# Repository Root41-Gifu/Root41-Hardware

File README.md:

# Root41-Hardware
Root41のハードウェア開発リポジトリです。

3D設計のリンクはこちら↓

[Root41 2021-2022](https://a360.co/2STp2Ga)

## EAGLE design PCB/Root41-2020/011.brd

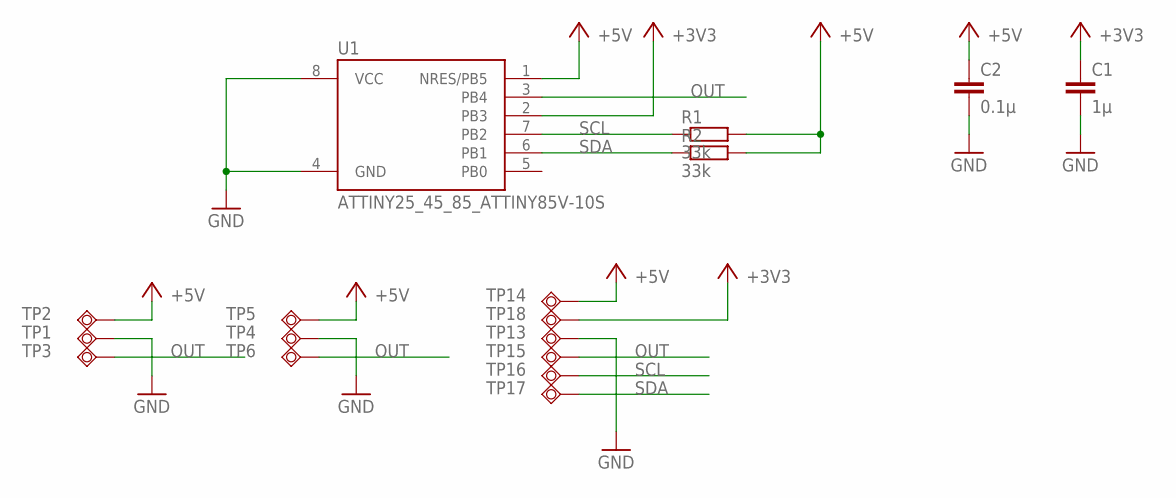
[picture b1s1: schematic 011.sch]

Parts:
C1: 1μ; C0603
C2: 0.1μ; C0603
R1, R2: 33k; R0603
TP1, TP3, TP4, TP6, TP13, TP15, TP16, TP17, TP18: TPSQTP11R; TP11R
TP2, TP5, TP14: TPSQTP11SQ; TP11SQ
U1: ATTINY25_45_85_ATTINY85V-10S; ATTINY25_45_85_SOIC8_EIAJ_208MIL

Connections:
+3V3: C1.1, TP18.TP, U1.2 (PB3)
+5V: C2.1, R1.2, R2.2, TP2.TP, TP5.TP, TP14.TP, U1.1 (NRES/PB5)
GND: C1.2, C2.2, TP1.TP, TP4.TP, TP13.TP, U1.4 (GND), U1.8 (VCC)
OUT: TP3.TP, TP6.TP, TP15.TP, U1.3 (PB4)
SCL: R1.1, TP16.TP, U1.7 (PB2)
SDA: R2.1, TP17.TP, U1.6 (PB1)

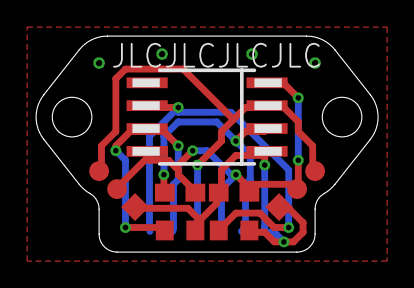
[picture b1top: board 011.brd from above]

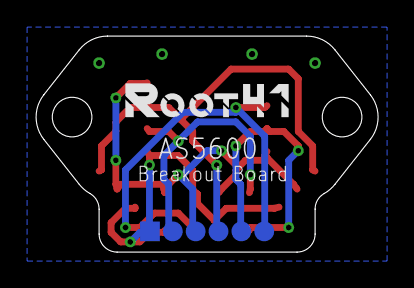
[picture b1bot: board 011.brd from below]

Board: 2 copper layers, 19.0 x 12.0 mm, 17 parts (6 on the bottom side), 6 nets.

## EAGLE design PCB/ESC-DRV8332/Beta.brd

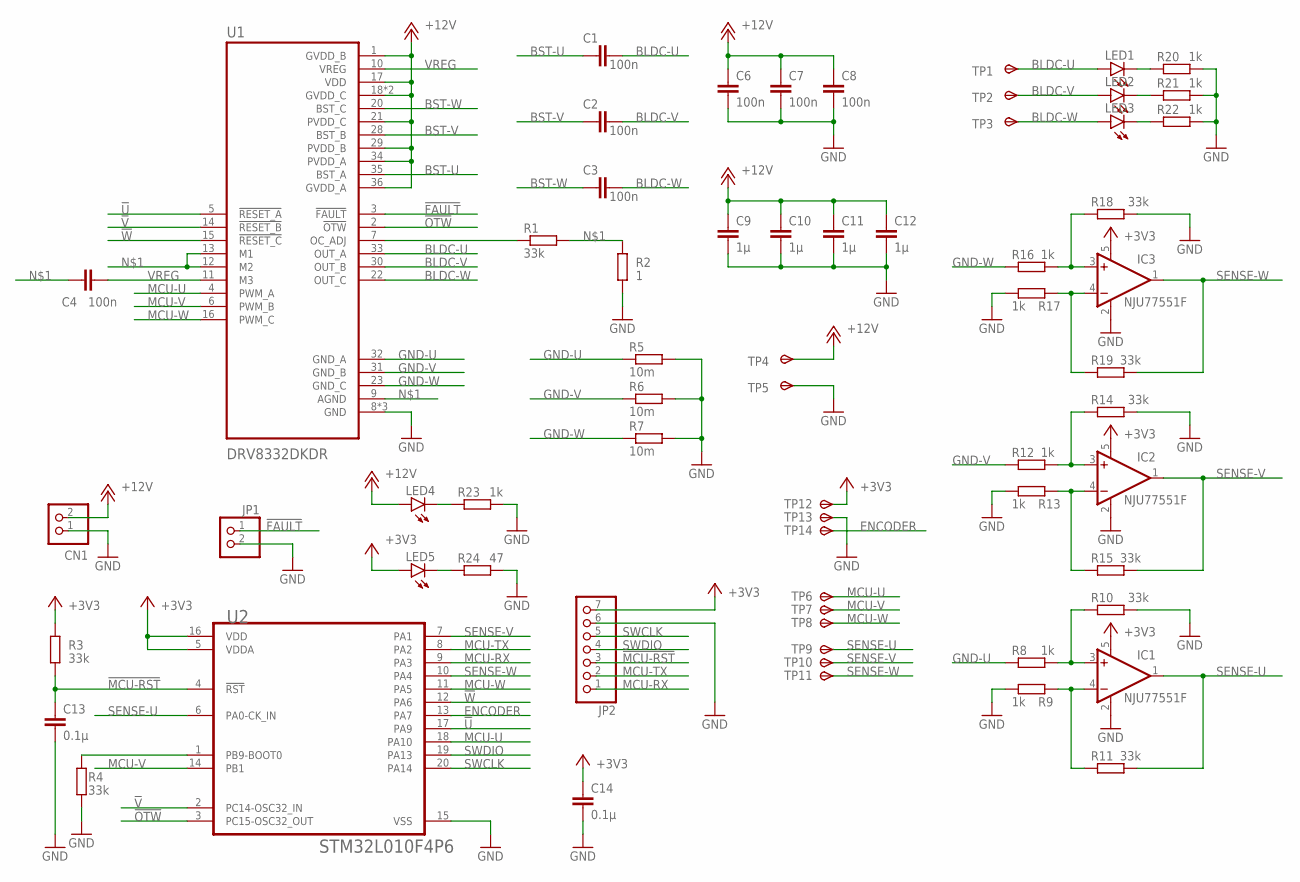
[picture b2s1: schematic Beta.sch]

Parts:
C1, C2, C3, C4, C6, C7, C8: 100n; C0603
C9, C10, C11, C12: 1μ; C0603
C13, C14: 0.1μ; C0603
CN1: B2B-PH-K-S
IC1, IC2, IC3: NJU77551F; SOT23-5
JP1: PINHD-1X2/90; 1X02/90
JP2: PINHD-1X7/90; 1X07/90
LED1, LED2, LED3, LED4, LED5: LEDCHIPLED_0603; CHIPLED_0603
R1, R3, R4, R10, R11, R14, R15, R18, R19: 33k; R0603
R2: 1; R0603
R5, R6, R7: 10m; R3216
R8, R9, R12, R13, R16, R17, R20, R21, R22, R23: 1k; R0603
R24: 47; R0603
TP1, TP2, TP3, TP4, TP5: TPSPAD1-20; P1-20
TP6, TP9, TP12: TPSTP11SQ; TP11SQ
TP7, TP8, TP10, TP11, TP13, TP14: TPSTP11R; TP11R
U1: DRV8332DKDR; SOP65P1420X360-36N
U2: STMICROELECTRONICS_STM32L010F4P6STMICROELECTRONIC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; STMICROELECTRONICS_STM32L010F4P6_2

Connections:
!FAULT: JP1.1, U1.3 (!FAULT)
!MCU-RST: C13.1, JP2.3, R3.1, U2.4 (!RST!)
!OTW: U1.2 (!OTW), U2.3 (PC15-OSC32_OUT)
!U: U1.5 (!RESET_A), U2.17 (PA9)
!V: U1.14 (!RESET_B), U2.2 (PC14-OSC32_IN)
!W: U1.15 (!RESET_C), U2.12 (PA6)
+3V3: C14.1, IC1.5 (V+), IC2.5 (V+), IC3.5 (V+), JP2.7, LED5.A, R3.2, TP12.TP, U2.5 (VDDA), U2.16 (VDD)
+12V: C6.1, C7.1, C8.1, C9.1, C10.1, C11.1, C12.1, CN1.2, LED4.A, TP4.TP, U1.1 (GVDD_B), U1.17 (VDD), U1.18 (GVDD_C), U1.19 (GVDD_C), U1.21 (PVDD_C), U1.29 (PVDD_B), U1.34 (PVDD_A), U1.36 (GVDD_A)
BLDC-U: C1.1, LED1.A, TP1.TP, U1.33 (OUT_A)
BLDC-V: C2.1, LED2.A, TP2.TP, U1.30 (OUT_B)
BLDC-W: C3.1, LED3.A, TP3.TP, U1.22 (OUT_C)
BST-U: C1.2, U1.35 (BST_A)
BST-V: C2.2, U1.28 (BST_B)
BST-W: C3.2, U1.20 (BST_C)
ENCODER: TP14.TP, U2.13 (PA7)
GND: C6.2, C7.2, C8.2, C9.2, C10.2, C11.2, C12.2, C13.2, C14.2, CN1.1, IC1.2 (V-), IC2.2 (V-), IC3.2 (V-), JP1.2, JP2.6, R2.1, R4.1, R5.2, R6.2, R7.2, R9.1, R10.2, R13.1, R14.2, R17.1, R18.2, R20.2, R21.2, R22.2, R23.2, R24.2, TP5.TP, TP13.TP, U1.8 (GND), U1.24 (GND), U1.25 (GND), U2.15 (VSS)
GND-U: R5.1, R8.1, U1.32 (GND_A)
GND-V: R6.1, R12.1, U1.31 (GND_B)
GND-W: R7.1, R16.1, U1.23 (GND_C)
MCU-RX: JP2.1, U2.9 (PA3)
MCU-TX: JP2.2, U2.8 (PA2)
MCU-U: TP6.TP, U1.4 (PWM_A), U2.18 (PA10)
MCU-V: TP7.TP, U1.6 (PWM_B), U2.14 (PB1)
MCU-W: TP8.TP, U1.16 (PWM_C), U2.11 (PA5)
unnamed: C4.1, R1.2, R2.2, U1.9 (AGND), U1.12 (M2), U1.13 (M1)
unnamed: R4.2, U2.1 (PB9-BOOT0)
unnamed: R1.1, U1.7 (OC_ADJ)
unnamed: IC1.3 (+IN), R8.2, R10.1
unnamed: IC2.3 (+IN), R12.2, R14.1
unnamed: IC1.4 (-IN), R9.2, R11.1
unnamed: IC2.4 (-IN), R13.2, R15.1
unnamed: IC3.3 (+IN), R16.2, R18.1
unnamed: IC3.4 (-IN), R17.2, R19.1
unnamed: LED1.C, R20.1
unnamed: LED2.C, R21.1
unnamed: LED3.C, R22.1
unnamed: LED4.C, R23.1
unnamed: LED5.C, R24.1
SENSE-U: IC1.1 (OUT), R11.2, TP9.TP, U2.6 (PA0-CK_IN)
SENSE-V: IC2.1 (OUT), R15.2, TP10.TP, U2.7 (PA1)
SENSE-W: IC3.1 (OUT), R19.2, TP11.TP, U2.10 (PA4)
SWCLK: JP2.5, U2.20 (PA14)
SWDIO: JP2.4, U2.19 (PA13)
VREG: C4.2, U1.10 (VREG), U1.11 (M3)

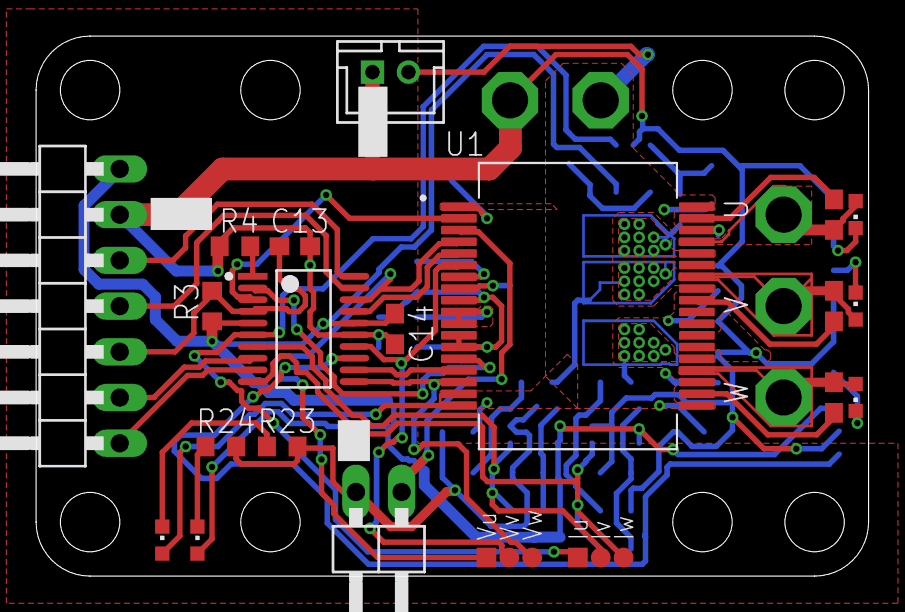
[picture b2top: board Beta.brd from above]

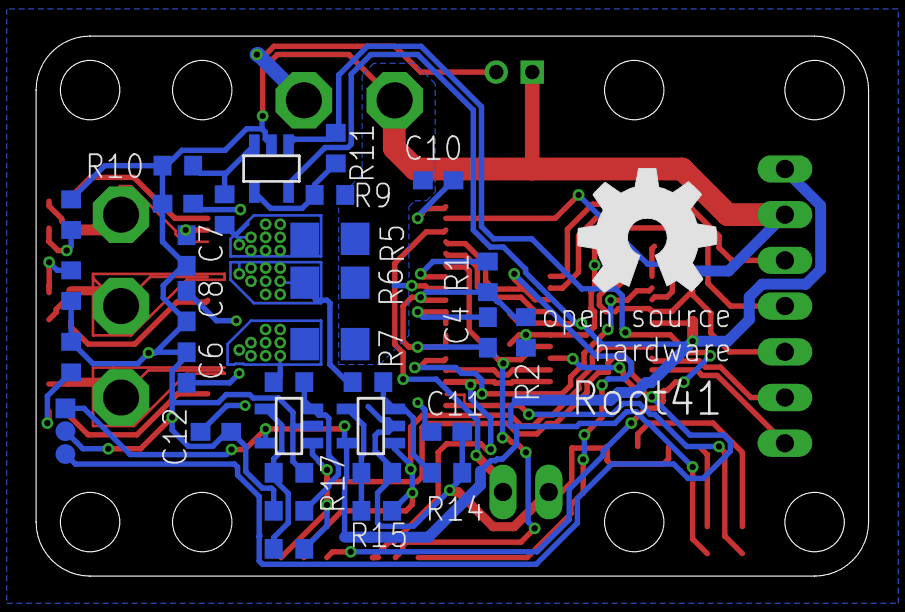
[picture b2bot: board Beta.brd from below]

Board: 2 copper layers, 46.2 x 30.0 mm, 65 parts (35 on the bottom side), 44 nets.

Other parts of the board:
U$1: OSHW_8MM

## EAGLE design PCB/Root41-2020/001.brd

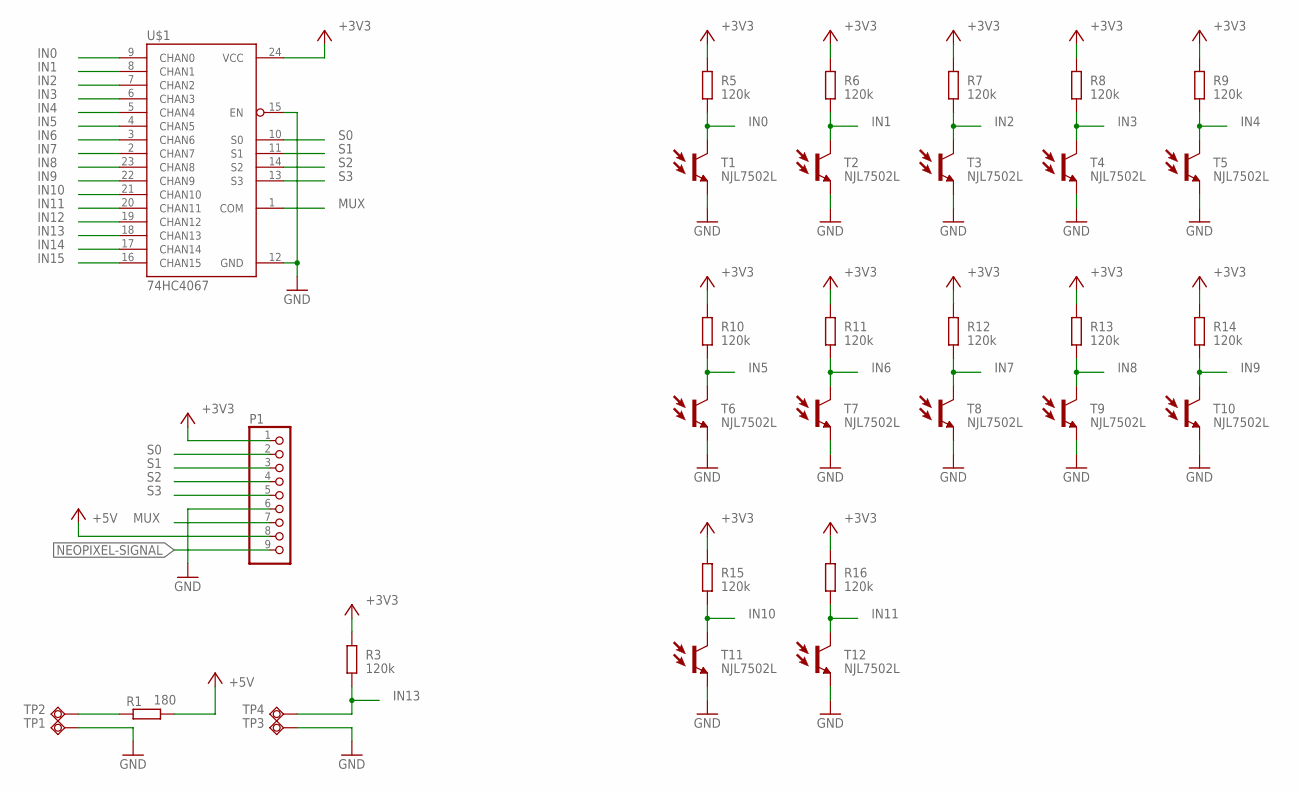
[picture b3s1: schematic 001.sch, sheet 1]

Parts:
P1: S9B-ZR-SM4A-TF; ZH-SM4-SIDE09
R1: 180; R2012
R3, R5, R6, R7, R8, R9, R10, R11, R12, R13, R14, R15, R16: 120k; R0805
T1, T2, T3, T4, T5, T6, T7, T8, T9, T10, T11, T12: NJL7502L; MYPARTS_NJL7502L
TP1, TP3: TPSQTP11R; TP11R
TP2, TP4: TPSQTP11SQ; TP11SQ
U$1: 74HC4067; SPARKFUN_SSOP24

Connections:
+3V3: P1.1, R3.1, R5.1, R6.1, R7.1, R8.1, R9.1, R10.1, R11.1, R12.1, R13.1, R14.1, R15.1, R16.1, U$1.24 (VCC)
+5V: P1.8, R1.2; also elsewhere on the board
GND: P1.6, T1.E, T2.E, T3.E, T4.E, T5.E, T6.E, T7.E, T8.E, T9.E, T10.E, T11.E, T12.E, TP1.TP, TP3.TP, U$1.12 (GND), U$1.15 (EN); also elsewhere on the board
IN0: R5.2, T1.C, U$1.9 (CHAN0)
IN1: R6.2, T2.C, U$1.8 (CHAN1)
IN2: R7.2, T3.C, U$1.7 (CHAN2)
IN3: R8.2, T4.C, U$1.6 (CHAN3)
IN4: R9.2, T5.C, U$1.5 (CHAN4)
IN5: R10.2, T6.C, U$1.4 (CHAN5)
IN6: R11.2, T7.C, U$1.3 (CHAN6)
IN7: R12.2, T8.C, U$1.2 (CHAN7)
IN8: R13.2, T9.C, U$1.23 (CHAN8)
IN9: R14.2, T10.C, U$1.22 (CHAN9)
IN10: R15.2, T11.C, U$1.21 (CHAN10)
IN11: R16.2, T12.C, U$1.20 (CHAN11)
IN12: U$1.19 (CHAN12)
IN13: R3.2, TP4.TP, U$1.18 (CHAN13)
IN14: U$1.17 (CHAN14)
IN15: U$1.16 (CHAN15)
MUX: P1.7, U$1.1 (COM)
unnamed: R1.1, TP2.TP
NEOPIXEL-SIGNAL: P1.9; also elsewhere on the board
S0: P1.2, U$1.10 (S0)
S1: P1.3, U$1.11 (S1)
S2: P1.4, U$1.14 (S2)
S3: P1.5, U$1.13 (S3)

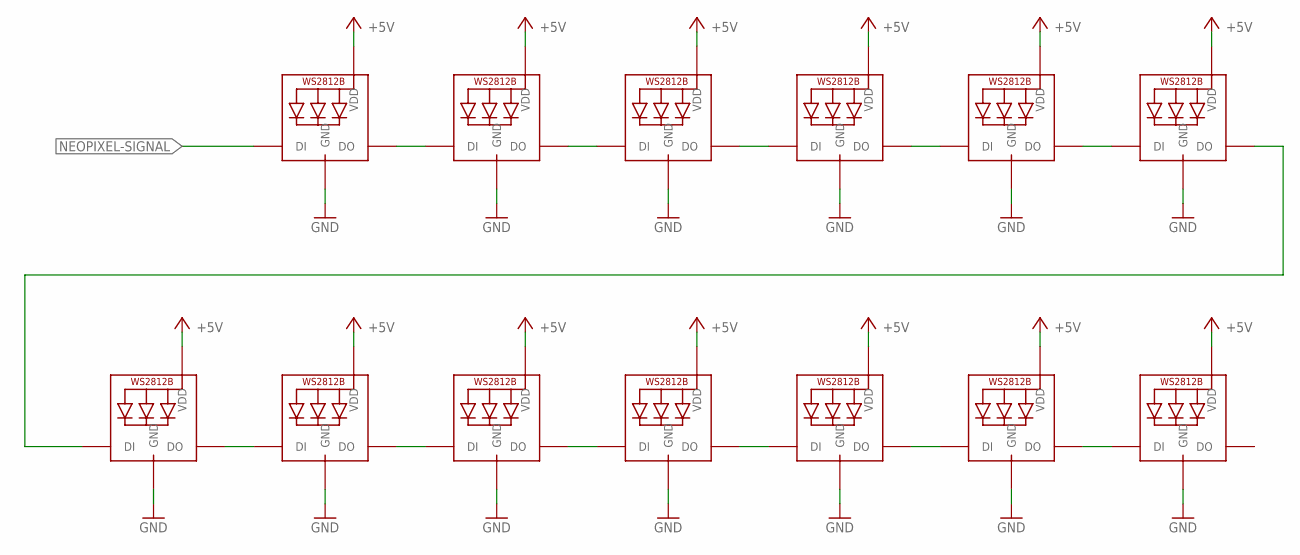
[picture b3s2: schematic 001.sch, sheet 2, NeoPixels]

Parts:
LED1, LED2, LED3, LED4, LED5, LED6, LED7, LED8, LED9, LED10, LED11, LED12, LED13: WS2812B5050; WS2812B

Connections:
+5V: LED1.1-VDD (VDD), LED2.1-VDD (VDD), LED3.1-VDD (VDD), LED4.1-VDD (VDD), LED5.1-VDD (VDD), LED6.1-VDD (VDD), LED7.1-VDD (VDD), LED8.1-VDD (VDD), LED9.1-VDD (VDD), LED10.1-VDD (VDD), LED11.1-VDD (VDD), LED12.1-VDD (VDD), LED13.1-VDD (VDD); also elsewhere on the board
GND: LED1.3-GND (GND), LED2.3-GND (GND), LED3.3-GND (GND), LED4.3-GND (GND), LED5.3-GND (GND), LED6.3-GND (GND), LED7.3-GND (GND), LED8.3-GND (GND), LED9.3-GND (GND), LED10.3-GND (GND), LED11.3-GND (GND), LED12.3-GND (GND), LED13.3-GND (GND); also elsewhere on the board
unnamed: LED2.2-DOUT (DO), LED3.4-DIN (DI)
unnamed: LED1.2-DOUT (DO), LED2.4-DIN (DI)
unnamed: LED3.2-DOUT (DO), LED4.4-DIN (DI)
unnamed: LED4.2-DOUT (DO), LED5.4-DIN (DI)
unnamed: LED5.2-DOUT (DO), LED6.4-DIN (DI)
unnamed: LED6.2-DOUT (DO), LED7.4-DIN (DI)
unnamed: LED7.2-DOUT (DO), LED8.4-DIN (DI)
unnamed: LED8.2-DOUT (DO), LED9.4-DIN (DI)
unnamed: LED9.2-DOUT (DO), LED10.4-DIN (DI)
unnamed: LED10.2-DOUT (DO), LED11.4-DIN (DI)
unnamed: LED11.2-DOUT (DO), LED12.4-DIN (DI)
unnamed: LED12.2-DOUT (DO), LED13.4-DIN (DI)
NEOPIXEL-SIGNAL: LED1.4-DIN (DI); also elsewhere on the board

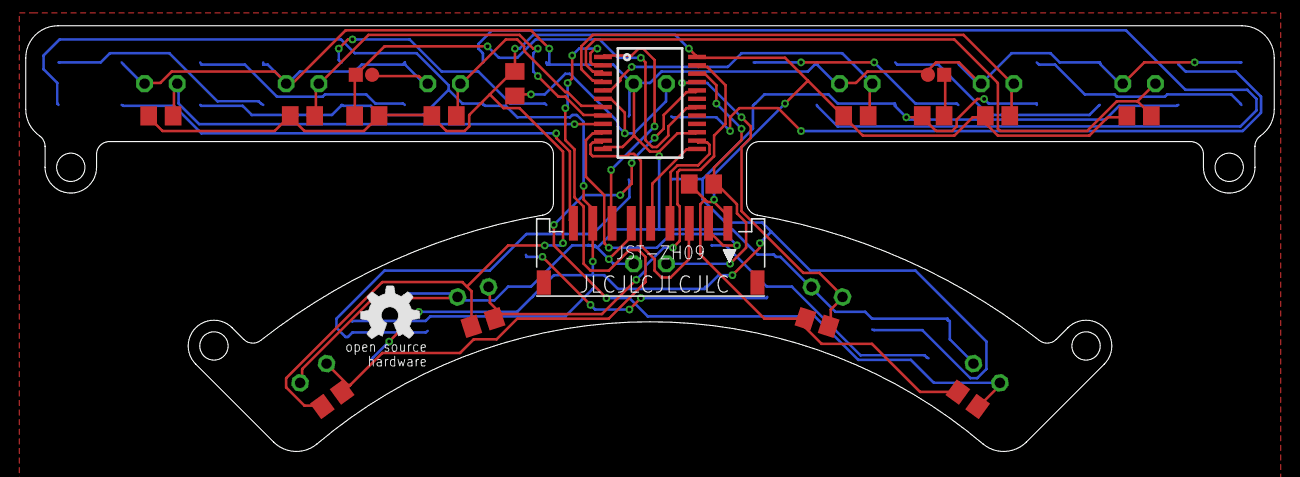
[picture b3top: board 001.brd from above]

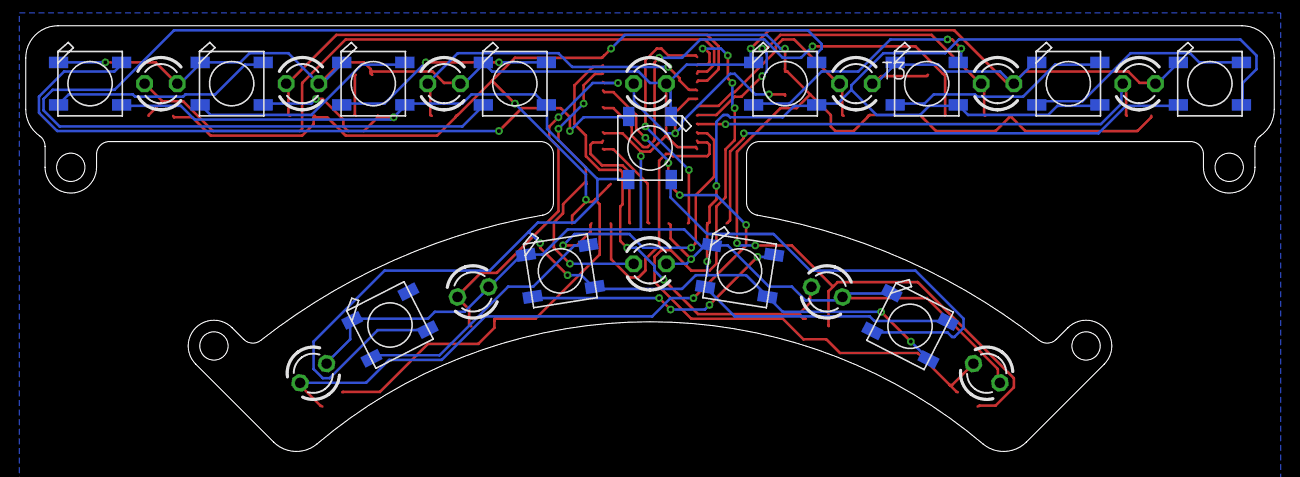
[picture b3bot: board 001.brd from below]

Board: 2 copper layers, 97.0 x 33.1 mm, 46 parts (25 on the bottom side), 35 nets.

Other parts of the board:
U$2: OSHW_5MM

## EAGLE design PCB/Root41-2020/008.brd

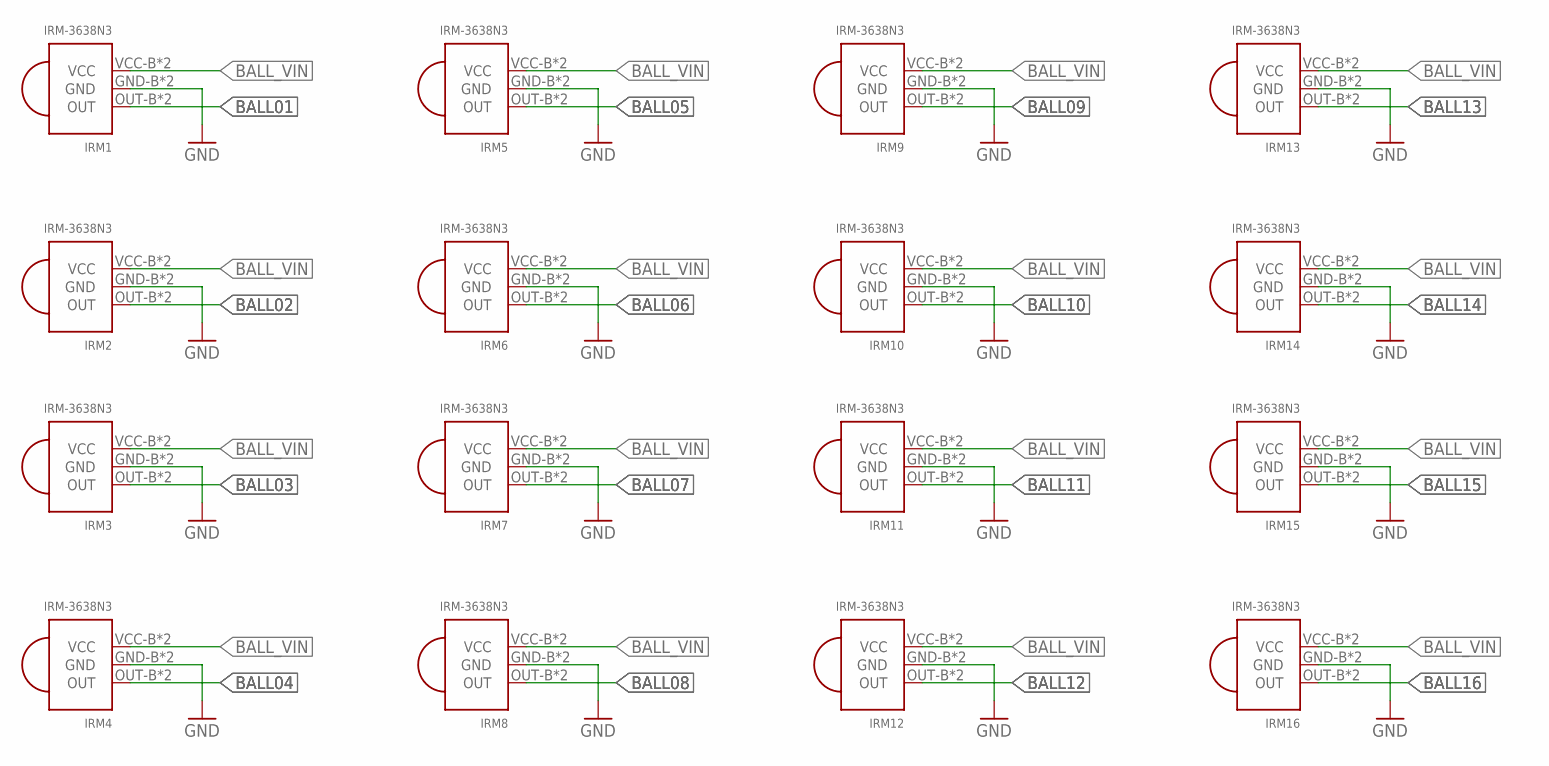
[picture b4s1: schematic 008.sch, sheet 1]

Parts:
IRM1, IRM2, IRM3, IRM4, IRM5, IRM6, IRM7, IRM8, IRM9, IRM10, IRM11, IRM12, IRM13, IRM14, IRM15, IRM16: IRM-3638N3; MYPARTS_IRM_3633N3

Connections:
BALL01: IRM1.OUT-B (OUT), IRM1.OUT-T (OUT); also elsewhere on the board
BALL02: IRM2.OUT-B (OUT), IRM2.OUT-T (OUT); also elsewhere on the board
BALL03: IRM3.OUT-B (OUT), IRM3.OUT-T (OUT); also elsewhere on the board
BALL04: IRM4.OUT-B (OUT), IRM4.OUT-T (OUT); also elsewhere on the board
BALL05: IRM5.OUT-B (OUT), IRM5.OUT-T (OUT); also elsewhere on the board
BALL06: IRM6.OUT-B (OUT), IRM6.OUT-T (OUT); also elsewhere on the board
BALL07: IRM7.OUT-B (OUT), IRM7.OUT-T (OUT); also elsewhere on the board
BALL08: IRM8.OUT-B (OUT), IRM8.OUT-T (OUT); also elsewhere on the board
BALL09: IRM9.OUT-B (OUT), IRM9.OUT-T (OUT); also elsewhere on the board
BALL10: IRM10.OUT-B (OUT), IRM10.OUT-T (OUT); also elsewhere on the board
BALL11: IRM11.OUT-B (OUT), IRM11.OUT-T (OUT); also elsewhere on the board
BALL12: IRM12.OUT-B (OUT), IRM12.OUT-T (OUT); also elsewhere on the board
BALL13: IRM13.OUT-B (OUT), IRM13.OUT-T (OUT); also elsewhere on the board
BALL14: IRM14.OUT-B (OUT), IRM14.OUT-T (OUT); also elsewhere on the board
BALL15: IRM15.OUT-B (OUT), IRM15.OUT-T (OUT); also elsewhere on the board
BALL16: IRM16.OUT-B (OUT), IRM16.OUT-T (OUT); also elsewhere on the board
BALL_VIN: IRM1.VCC-B (VCC), IRM1.VCC-T (VCC), IRM2.VCC-B (VCC), IRM2.VCC-T (VCC), IRM3.VCC-B (VCC), IRM3.VCC-T (VCC), IRM4.VCC-B (VCC), IRM4.VCC-T (VCC), IRM5.VCC-B (VCC), IRM5.VCC-T (VCC), IRM6.VCC-B (VCC), IRM6.VCC-T (VCC), IRM7.VCC-B (VCC), IRM7.VCC-T (VCC), IRM8.VCC-B (VCC), IRM8.VCC-T (VCC), IRM9.VCC-B (VCC), IRM9.VCC-T (VCC), IRM10.VCC-B (VCC), IRM10.VCC-T (VCC), IRM11.VCC-B (VCC), IRM11.VCC-T (VCC), IRM12.VCC-B (VCC), IRM12.VCC-T (VCC), IRM13.VCC-B (VCC), IRM13.VCC-T (VCC), IRM14.VCC-B (VCC), IRM14.VCC-T (VCC), IRM15.VCC-B (VCC), IRM15.VCC-T (VCC), IRM16.VCC-B (VCC), IRM16.VCC-T (VCC); also elsewhere on the board
GND: IRM1.GND-B (GND), IRM1.GND-T (GND), IRM2.GND-B (GND), IRM2.GND-T (GND), IRM3.GND-B (GND), IRM3.GND-T (GND), IRM4.GND-B (GND), IRM4.GND-T (GND), IRM5.GND-B (GND), IRM5.GND-T (GND), IRM6.GND-B (GND), IRM6.GND-T (GND), IRM7.GND-B (GND), IRM7.GND-T (GND), IRM8.GND-B (GND), IRM8.GND-T (GND), IRM9.GND-B (GND), IRM9.GND-T (GND), IRM10.GND-B (GND), IRM10.GND-T (GND), IRM11.GND-B (GND), IRM11.GND-T (GND), IRM12.GND-B (GND), IRM12.GND-T (GND), IRM13.GND-B (GND), IRM13.GND-T (GND), IRM14.GND-B (GND), IRM14.GND-T (GND), IRM15.GND-B (GND), IRM15.GND-T (GND), IRM16.GND-B (GND), IRM16.GND-T (GND); also elsewhere on the board

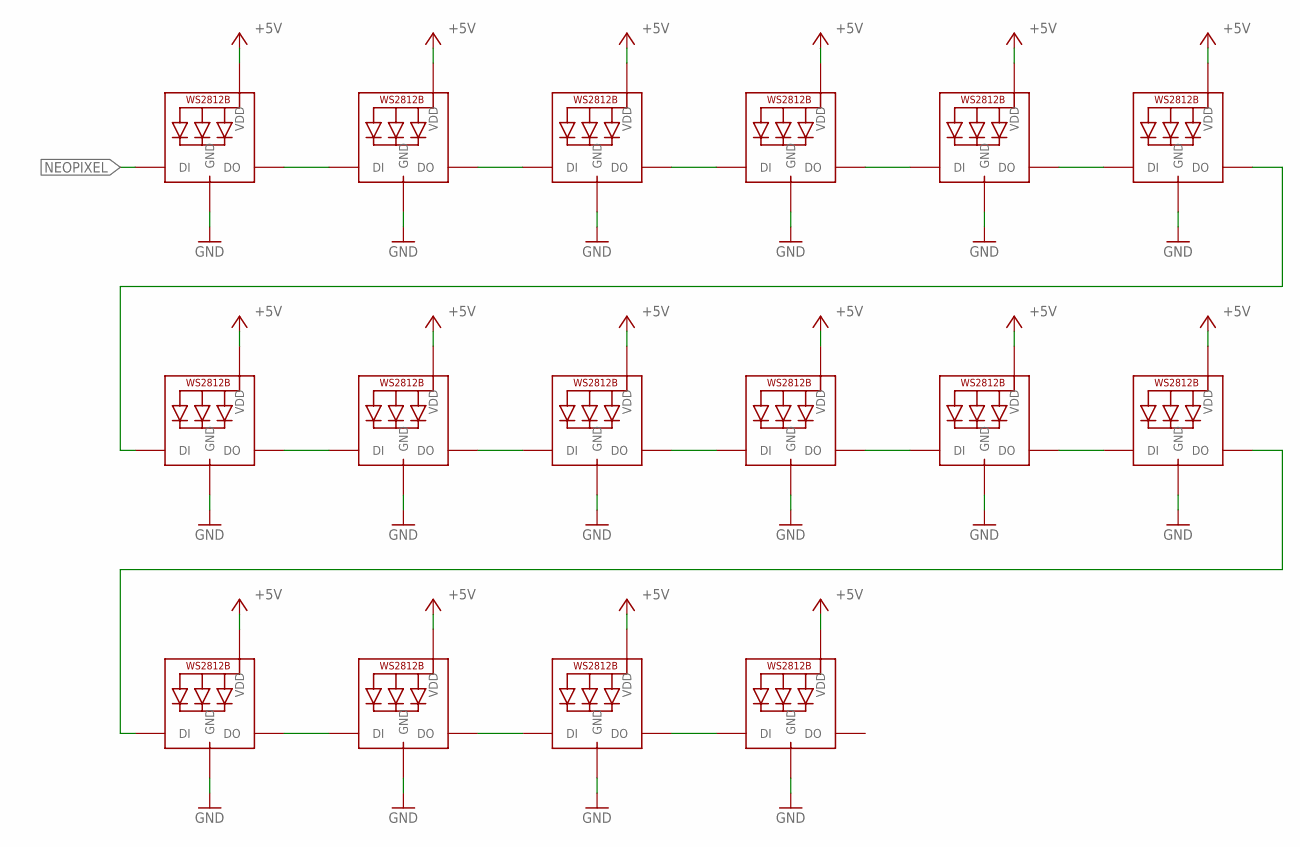
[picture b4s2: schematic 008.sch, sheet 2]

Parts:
LED1, LED2, LED3, LED4, LED5, LED6, LED7, LED8, LED9, LED10, LED11, LED12, LED13, LED14, LED15, LED16: WS2812B5050; WS2812B

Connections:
+5V: LED1.1-VDD (VDD), LED2.1-VDD (VDD), LED3.1-VDD (VDD), LED4.1-VDD (VDD), LED5.1-VDD (VDD), LED6.1-VDD (VDD), LED7.1-VDD (VDD), LED8.1-VDD (VDD), LED9.1-VDD (VDD), LED10.1-VDD (VDD), LED11.1-VDD (VDD), LED12.1-VDD (VDD), LED13.1-VDD (VDD), LED14.1-VDD (VDD), LED15.1-VDD (VDD), LED16.1-VDD (VDD); also elsewhere on the board
GND: LED1.3-GND (GND), LED2.3-GND (GND), LED3.3-GND (GND), LED4.3-GND (GND), LED5.3-GND (GND), LED6.3-GND (GND), LED7.3-GND (GND), LED8.3-GND (GND), LED9.3-GND (GND), LED10.3-GND (GND), LED11.3-GND (GND), LED12.3-GND (GND), LED13.3-GND (GND), LED14.3-GND (GND), LED15.3-GND (GND), LED16.3-GND (GND); also elsewhere on the board
unnamed: LED12.2-DOUT (DO), LED13.4-DIN (DI)
unnamed: LED6.2-DOUT (DO), LED7.4-DIN (DI)
NEOPIXEL: LED1.4-DIN (DI); also elsewhere on the board
NEOPIXEL1: LED1.2-DOUT (DO), LED2.4-DIN (DI)
NEOPIXEL2: LED2.2-DOUT (DO), LED3.4-DIN (DI)
NEOPIXEL3: LED3.2-DOUT (DO), LED4.4-DIN (DI)
NEOPIXEL4: LED4.2-DOUT (DO), LED5.4-DIN (DI)
NEOPIXEL5: LED5.2-DOUT (DO), LED6.4-DIN (DI)
NEOPIXEL6: LED7.2-DOUT (DO), LED8.4-DIN (DI)
NEOPIXEL7: LED8.2-DOUT (DO), LED9.4-DIN (DI)
NEOPIXEL8: LED9.2-DOUT (DO), LED10.4-DIN (DI)
NEOPIXEL9: LED10.2-DOUT (DO), LED11.4-DIN (DI)
NEOPIXEL10: LED11.2-DOUT (DO), LED12.4-DIN (DI)
NEOPIXEL11: LED13.2-DOUT (DO), LED14.4-DIN (DI)
NEOPIXEL12: LED14.2-DOUT (DO), LED15.4-DIN (DI)
NEOPIXEL13: LED15.2-DOUT (DO), LED16.4-DIN (DI)

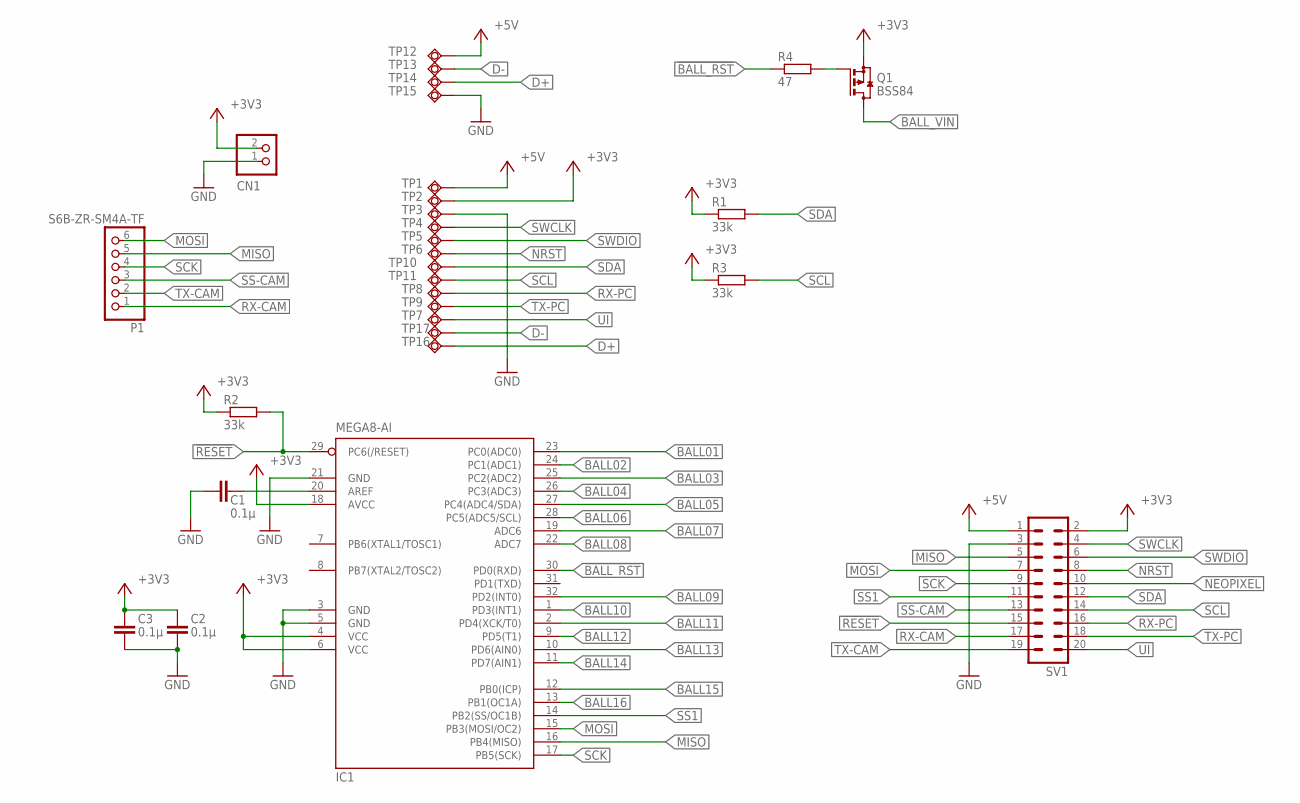
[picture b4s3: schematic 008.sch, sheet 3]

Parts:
C1, C2, C3: 0.1μ; C1608
CN1: S2B-PH-SM4-TB
IC1: MEGA8-AI; TQFP32-08
P1: S6B-ZR-SM4A-TF; ZH-SM4-SIDE06
Q1: BSS84; SOT23
R1, R2, R3: 33k; R0603
R4: 47; R0603
SV1: ML20
TP1, TP12: TPSQTP10SQ; TP10SQ
TP2, TP3, TP4, TP5, TP6, TP7, TP8, TP9, TP10, TP11, TP13, TP14, TP15, TP16, TP17: TPSQTP10R; TP10R

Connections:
!BALL_RST: IC1.30 (PD0(RXD)), R4.1
!RESET: IC1.29 (PC6(/RESET)), R2.2, SV1.15
+3V3: C2.1, C3.1, CN1.2, IC1.4 (VCC), IC1.6 (VCC), IC1.18 (AVCC), Q1.2 (S), R1.1, R2.1, R3.1, SV1.2, TP2.TP
+5V: SV1.1, TP1.TP, TP12.TP; also elsewhere on the board
BALL01: IC1.23 (PC0(ADC0)); also elsewhere on the board
BALL02: IC1.24 (PC1(ADC1)); also elsewhere on the board
BALL03: IC1.25 (PC2(ADC2)); also elsewhere on the board
BALL04: IC1.26 (PC3(ADC3)); also elsewhere on the board
BALL05: IC1.27 (PC4(ADC4/SDA)); also elsewhere on the board
BALL06: IC1.28 (PC5(ADC5/SCL)); also elsewhere on the board
BALL07: IC1.19 (ADC6); also elsewhere on the board
BALL08: IC1.22 (ADC7); also elsewhere on the board
BALL09: IC1.32 (PD2(INT0)); also elsewhere on the board
BALL10: IC1.1 (PD3(INT1)); also elsewhere on the board
BALL11: IC1.2 (PD4(XCK/T0)); also elsewhere on the board
BALL12: IC1.9 (PD5(T1)); also elsewhere on the board
BALL13: IC1.10 (PD6(AIN0)); also elsewhere on the board
BALL14: IC1.11 (PD7(AIN1)); also elsewhere on the board
BALL15: IC1.12 (PB0(ICP)); also elsewhere on the board
BALL16: IC1.13 (PB1(OC1A)); also elsewhere on the board
BALL_VIN: Q1.3 (D); also elsewhere on the board
D+: TP14.TP, TP16.TP
D-: TP13.TP, TP17.TP
GND: C1.2, C2.2, C3.2, CN1.1, IC1.3 (GND), IC1.5 (GND), IC1.21 (GND), SV1.3, TP3.TP, TP15.TP; also elsewhere on the board
MISO: IC1.16 (PB4(MISO)), P1.5, SV1.5
MOSI: IC1.15 (PB3(MOSI/OC2)), P1.6, SV1.7
unnamed: C1.1, IC1.20 (AREF)
unnamed: Q1.1 (G), R4.2
NEOPIXEL: SV1.10; also elsewhere on the board
NRST: SV1.8, TP6.TP
RX-PC: SV1.16, TP8.TP
SCK: IC1.17 (PB5(SCK)), P1.4, SV1.9
SCL: R3.2, SV1.14, TP11.TP
SDA: R1.2, SV1.12, TP10.TP
SS1: IC1.14 (PB2(SS/OC1B)), SV1.11
SWCLK: SV1.4, TP4.TP
SWDIO: SV1.6, TP5.TP
TX-CAM: P1.2, SV1.19
TX-PC: SV1.18, TP9.TP
UI: SV1.20, TP7.TP

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
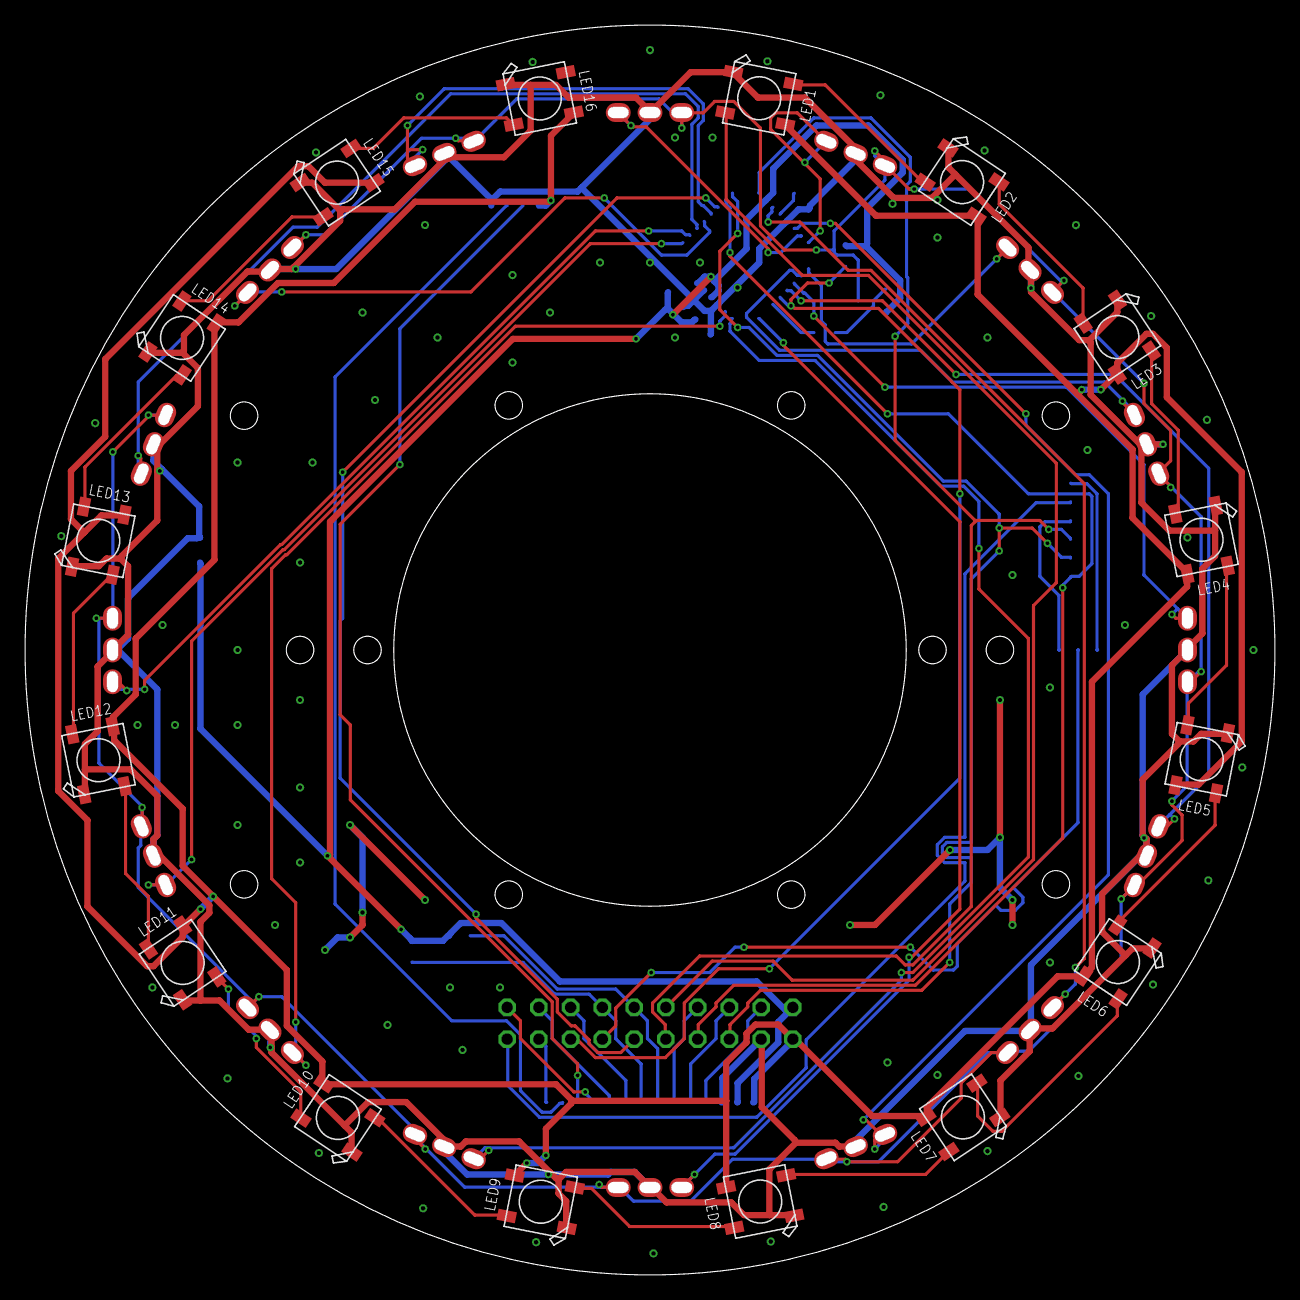
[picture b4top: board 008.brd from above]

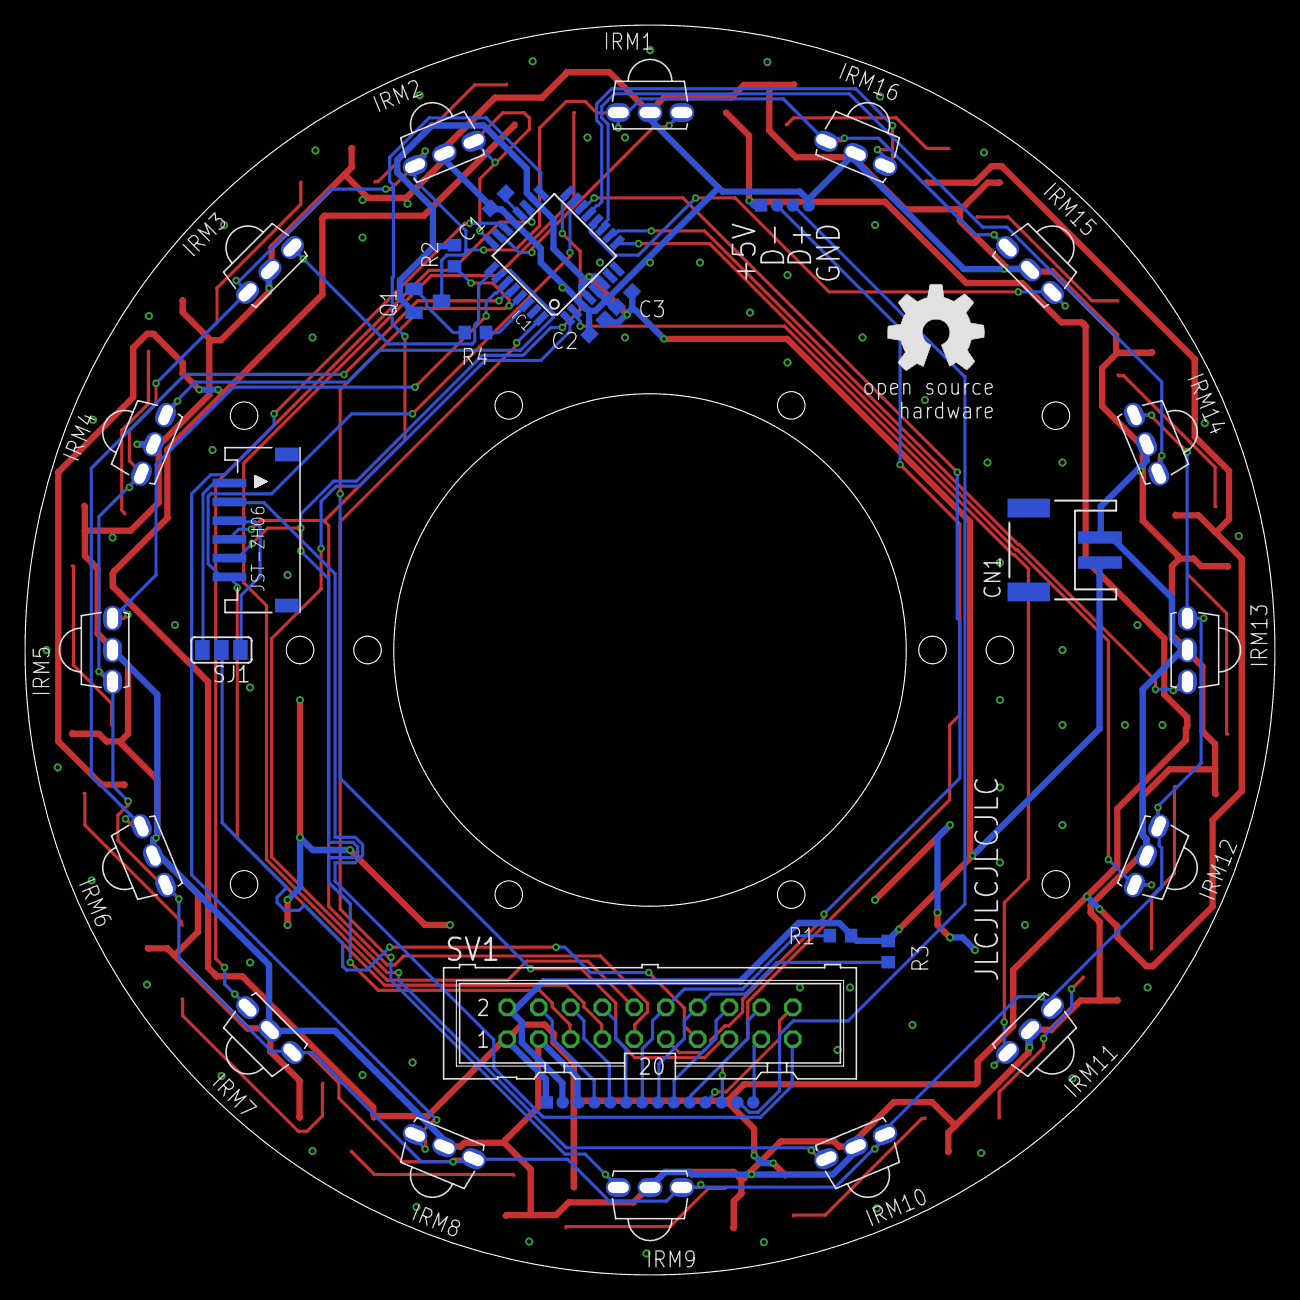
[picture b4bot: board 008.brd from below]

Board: 2 copper layers, 100.0 x 100.0 mm, 64 parts (48 on the bottom side), 59 nets.

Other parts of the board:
SJ1: SJ_2
TP18: TPSQTP10R; TP10R
U$1: OSHW_8MM

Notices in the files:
parts and their libraries:
COPYRIGHT: Copyright (C) 2018 Accelerated Designs. All rights reserved
